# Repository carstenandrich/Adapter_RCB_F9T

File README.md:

# u-blox RCB-F9T Adapter PCB w/ USB and SMA

Stackable adapter PCB for u-blox [RCB-F9T timing board](https://www.u-blox.com/en/product/rcb-f9t-timing-board) with the following features:

  * USB-to-UART converter (SiLabs CP2102)
  * fully USB-powered (option to supply RCB-F9T from low noise voltage source)
  * SMA connectors for TP1 and TP2 pins of RCB-F9T
  * SMA can drive 50 Ohm loads via buffer opamp (TI BUF602)

This repository contains KiCad EDA files of the PCB design and [JLCPCB fabrication files](./fabrication).

## Renderings of Adapter PCB with/without RCB-F9T

# Revisions

## Revision 1

Initial revision including JLCPCB fabrication files.

**Known Issues**:

  * RCB-F9T NRST pin is incorrectly treated as RST (pulled down via R41)
  * FB41 is too close to mounting hole

Board is fully operational after desoldering R41.

### Image of Adapter PCB with RCB-F9T

## Revision 2

Above issues fixed in EDA files (**not** fabrication files), but design was neither produced nor verified.

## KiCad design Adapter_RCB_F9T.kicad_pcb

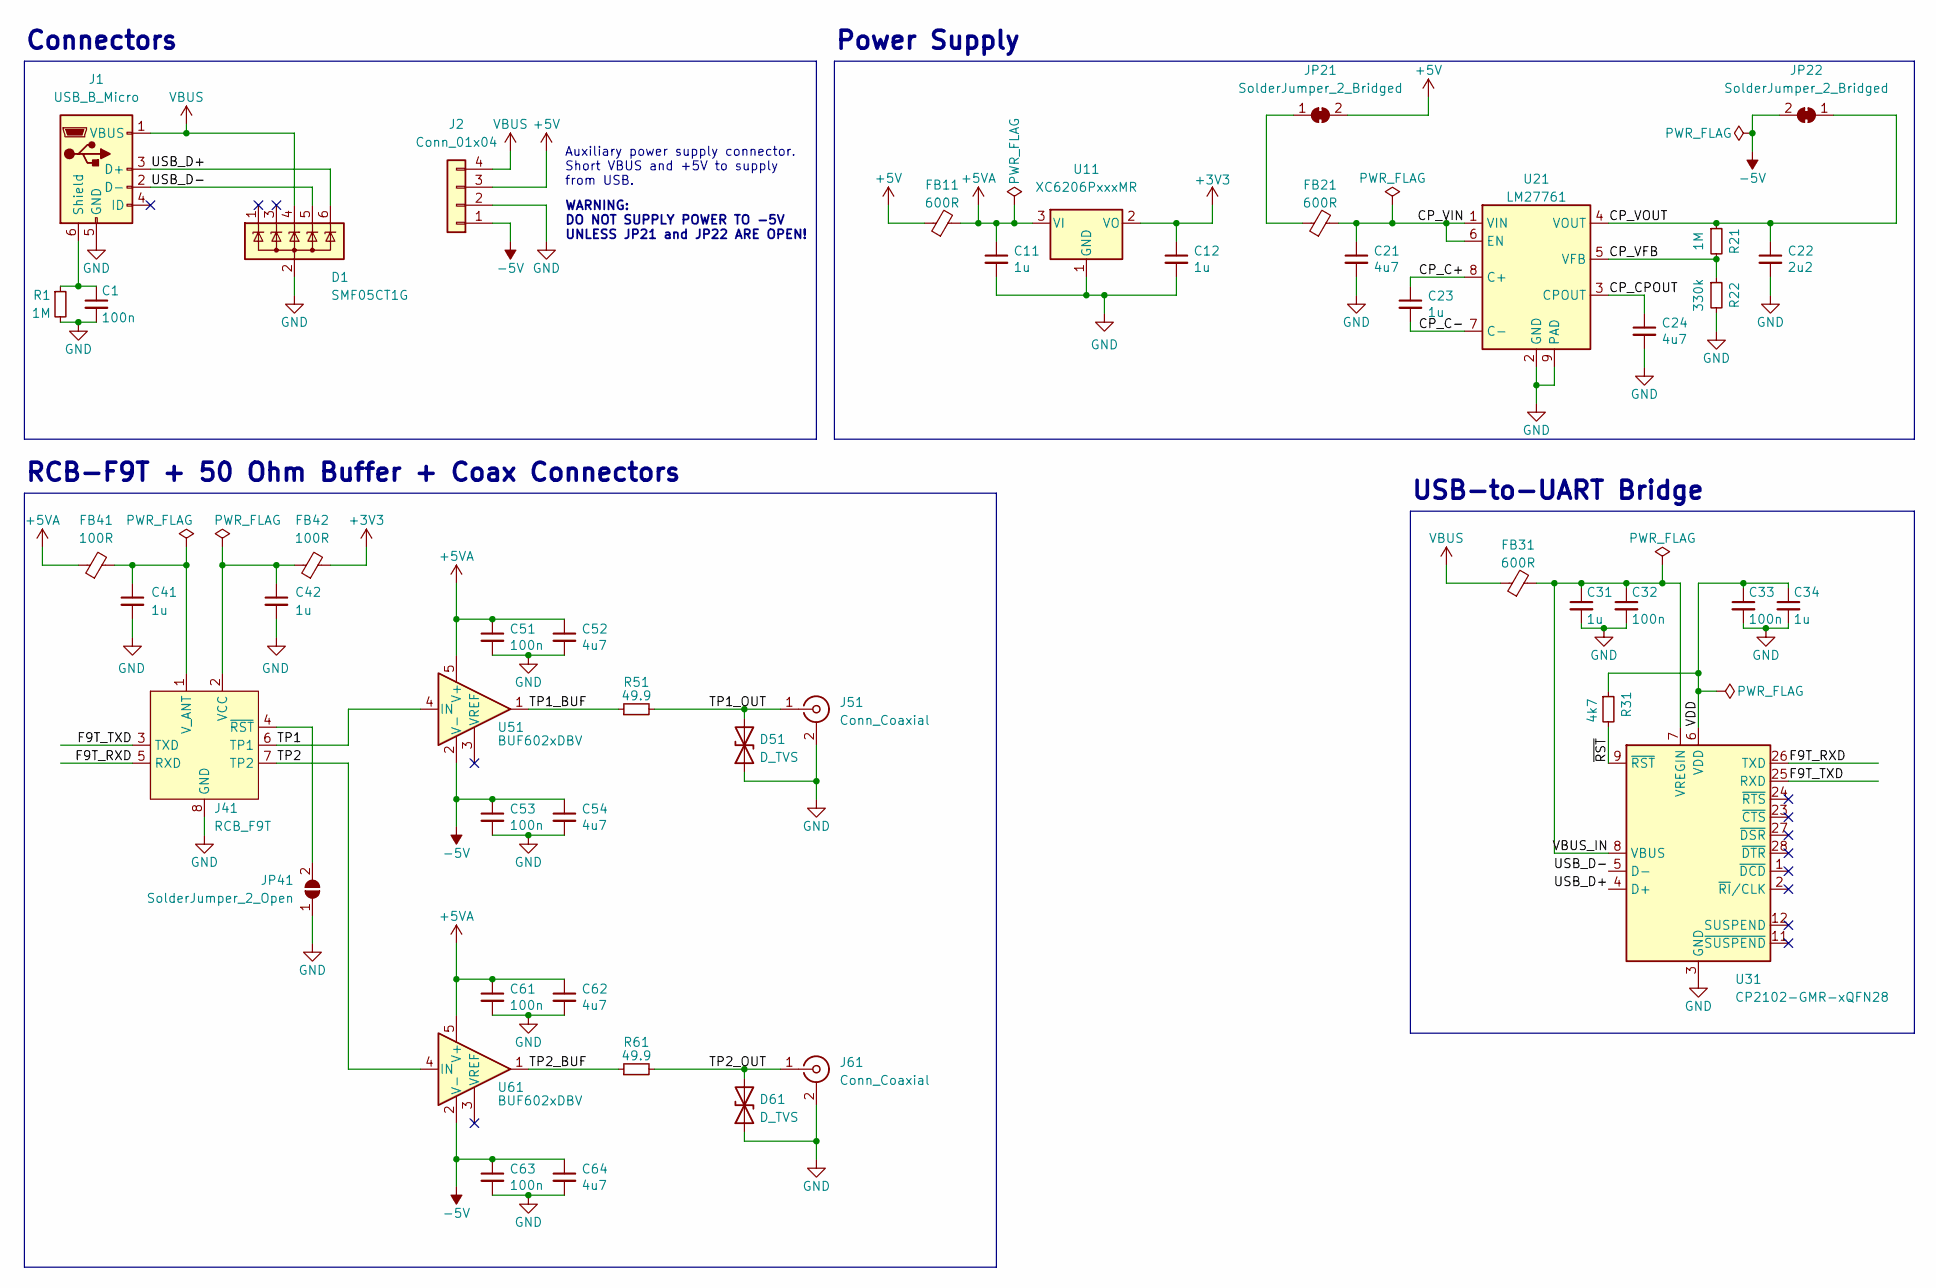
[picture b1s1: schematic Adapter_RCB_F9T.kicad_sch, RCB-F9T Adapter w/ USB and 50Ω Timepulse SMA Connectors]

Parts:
C1, C32, C33, C51, C53, C61, C63: 100n; C_0402_1005Metric; MPN CL05B104KB54PNC; LCSC C307331
C11, C12, C23, C31, C34, C41, C42: 1u; C_0603_1608Metric; MPN CL10A105KB8NNNC; LCSC C15849
C21, C24, C52, C54, C62, C64: 4u7; C_0603_1608Metric; MPN CL10A106MA8NRNC; LCSC C96446
C22: 2u2; C_0603_1608Metric; MPN CL10A475KO8NNNC; LCSC C19666
D1: SMF05CT1G; SOT-363_SC-70-6; LCSC C15879
D51, D61: D_TVS; D_0402_1005Metric; MPN 0402ESDA-05N; LCSC C316049
FB11, FB21, FB31: 600R; L_0805_2012Metric; LCSC C1017
FB41, FB42: 100R; L_0805_2012Metric; LCSC C1015
J1: USB_B_Micro; USB_Micro-B_Molex_47346-0001; LCSC C132560
J2: Conn_01x04; PinHeader_1x04_P2.54mm_Horizontal
J41: RCB_F9T
J51, J61: Conn_Coaxial; SMA_Rosenberger_32K145-400L5_EdgeMount_Horizontal; MPN 32K145-400L5
JP21, JP22: SolderJumper_2_Bridged; SolderJumper-2_P1.3mm_Bridged_RoundedPad1.0x1.5mm
JP41: SolderJumper_2_Open; SolderJumper-2_P1.3mm_Open_RoundedPad1.0x1.5mm
R1, R21: 1M; R_0402_1005Metric; MPN 0402WGF1004TCE; LCSC C26083
R22: 330k; R_0402_1005Metric; MPN 0402WGF3303TCE; LCSC C25778
R31: 4k7; R_0402_1005Metric; LCSC C25900
R51, R61: 49.9; R_0805_2012Metric; MPN R 49.9R 125mW 0805; LCSC C17720
U11: XC6206PxxxMR; SOT-23; LCSC C5446
U21: LM27761; WSON-8-1EP_2x2mm_P0.5mm_EP0.9x1.6mm; LCSC C129351
U31: CP2102-GMR-xQFN28; QFN-28-1EP_5x5mm_P0.5mm_EP3.35x3.35mm; LCSC C6568
U51, U61: BUF602xDBV; SOT-23-5; MPN BUF602xDBV

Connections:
+3V3: C12.1, FB42.2, U11.2 (VO)
+5V: FB11.1, J2.3, JP21.2 (B)
+5VA: C11.1, C51.1, C52.1, C61.1, C62.1, FB11.2, FB41.1, U11.3 (VI), U51.5 (V+), U61.5 (V+)
-5V: C53.1, C54.1, C63.1, C64.1, J2.1, JP22.2 (B), U51.2 (V-), U61.2 (V-)
/CP_C+: C23.1, U21.8 (C+)
/CP_C-: C23.2, U21.7 (C-)
/CP_CPOUT: C24.1, U21.3 (CPOUT)
/CP_VFB: R21.2, R22.1, U21.5 (VFB)
/CP_VIN: C21.1, FB21.2, U21.1 (VIN), U21.6 (EN)
/CP_VOUT: C22.1, JP22.1 (A), R21.1, U21.4 (VOUT)
/F9T_RXD: J41.5 (RXD), U31.26 (TXD)
/F9T_TXD: J41.3 (TXD), U31.25 (RXD)
/TP1: J41.6 (TP1), U51.4 (IN)
/TP1_BUF: R51.1, U51.1
/TP1_OUT: D51.2 (A2), J51.1 (In), R51.2
/TP2: J41.7 (TP2), U61.4 (IN)
/TP2_BUF: R61.1, U61.1
/TP2_OUT: D61.2 (A2), J61.1 (In), R61.2
/USB_D+: D1.6 (K), J1.3 (D+), U31.4 (D+)
/USB_D-: D1.5 (K), J1.2 (D-), U31.5 (D-)
/VBUS_IN: C31.1, C32.1, FB31.2, U31.7 (VREGIN), U31.8 (VBUS)
/VDD: C33.1, C34.1, R31.1, U31.6 (VDD)
/~RST: R31.2, U31.9 (~RST)
GND: C1.2, C11.2, C12.2, C21.2, C22.2, C24.2, C31.2, C32.2, C33.2, C34.2, C41.2, C42.2, C51.2, C52.2, C53.2, C54.2, C61.2, C62.2, C63.2, C64.2, D1.2 (A), D51.1 (A1), D61.1 (A1), J1.5 (GND), J2.2, J41.8 (GND), J51.2 (Ext), J61.2 (Ext), JP41.1 (A), R1.2, R22.2, U11.1 (GND), U21.2 (GND), U21.9 (PAD), U31.3 (GND), U31.29 (GND)
unnamed: C1.1, J1.6 (Shield), R1.1
unnamed: C42.1, FB42.1, J41.2 (VCC)
unnamed: C41.1, FB41.2, J41.1 (V_ANT)
unnamed: J41.4 (~RST), JP41.2 (B)
unnamed: FB21.1, JP21.1 (A)
VBUS: D1.4 (K), FB31.1, J1.1 (VBUS), J2.4

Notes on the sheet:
Auxiliary power supply connector. Short VBUS and +5V to supply from USB.
WARNING: DO NOT SUPPLY POWER TO -5V UNLESS JP21 and JP22 ARE OPEN!
Power Supply
Connectors
RCB-F9T + 50 Ohm Buffer + Coax Connectors
USB-to-UART Bridge

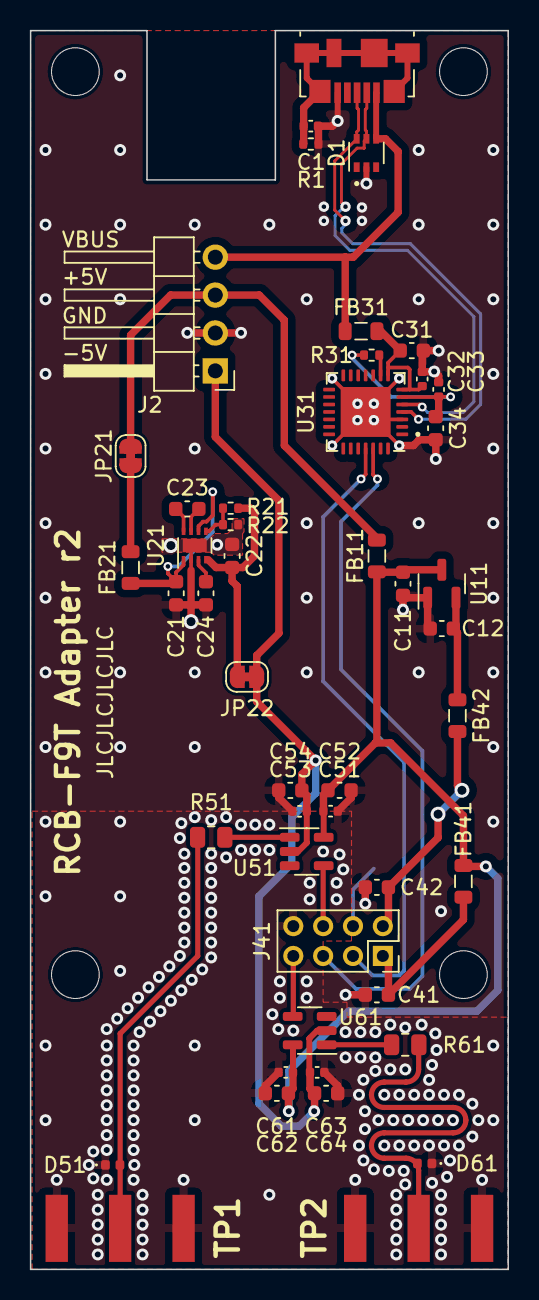
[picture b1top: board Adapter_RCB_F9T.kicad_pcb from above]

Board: 4 copper layers, 32.0 x 83.0 mm, 48 parts (1 on the bottom side), 30 nets.

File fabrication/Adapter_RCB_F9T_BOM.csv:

Comment,Designator,Footprint,LCSC Part #
"100n Unpolarized capacitor, small symbol","C1,C32,C33,C51,C53,C61,C63",C_0402_1005Metric,C307331
"1u Unpolarized capacitor, small symbol","C11,C12,C23,C31,C34,C41,C42",C_0603_1608Metric,C15849
"4u7 Unpolarized capacitor, small symbol","C21,C24,C52,C54,C62,C64",C_0603_1608Metric,C96446
"2u2 Unpolarized capacitor, small symbol",C22,C_0603_1608Metric,C19666
"SMF05CT1G TVS Diode Array, 5.5V Standoff, 5 Channels, SC-70-6 package",D1,SOT-363_SC-70-6,C15879
D_TVS Bidirectional transient-voltage-suppression diode,"D51,D61",D_0402_1005Metric,C316049
"600R Ferrite bead, small symbol","FB11,FB21,FB31",L_0805_2012Metric,C1017
"100R Ferrite bead, small symbol","FB41,FB42",L_0805_2012Metric,C1015
USB_B_Micro USB Micro Type B connector,J1,USB_Micro-B_Molex_47346-0001,C132560
"Conn_01x04 Generic connector, single row, 01x04, script generated (kicad-library-utils/schlib/autogen/connector/)",J2,PinHeader_1x04_P2.54mm_Horizontal,
RCB_F9T ,J41,RCB_F9T,
"Conn_Coaxial coaxial connector (BNC, SMA, SMB, SMC, Cinch/RCA, LEMO, ...)","J51,J61",SMA_Rosenberger_32K145-400L5_EdgeMount_Horizontal,
"SolderJumper_2_Bridged Solder Jumper, 2-pole, closed/bridged","JP21,JP22",SolderJumper-2_P1.3mm_Bridged_RoundedPad1.0x1.5mm,
"1M Resistor, small symbol","R1,R21",R_0402_1005Metric,C26083
"330k Resistor, small symbol",R22,R_0402_1005Metric,C25778
"4k7 Resistor, small symbol","R31,R41",R_0402_1005Metric,C25900
"49.9 Resistor, small symbol","R51,R61",R_0805_2012Metric,C17720
"XC6206PxxxMR Positive 60-250mA Low Dropout Regulator, Fixed Output, SOT-23",U11,SOT-23,C5446
"LM27761 low-noise regulated switched-capacitor voltage inverter with 2.7V-5.5V input to -1.5 to -5V Output Voltage, WSON-8",U21,WSON-8-1EP_2x2mm_P0.5mm_EP0.9x1.6mm,C129351
"CP2102-GMR-xQFN28 USB to UART master bridge, QFN-28",U31,QFN-28-1EP_5x5mm_P0.5mm_EP3.35x3.35mm,C6568
"BUF602xDBV High-Speed, 1000 MHz, Closed-Loop Buffer, SOT23-5","U51,U61",SOT-23-5,

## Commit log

2022-09-21 add revision 1 design and fabrication files
2023-06-09 fix RCB-F9T NRST issue and move FB41 further away from mounting hole
2023-06-10 add documentation
